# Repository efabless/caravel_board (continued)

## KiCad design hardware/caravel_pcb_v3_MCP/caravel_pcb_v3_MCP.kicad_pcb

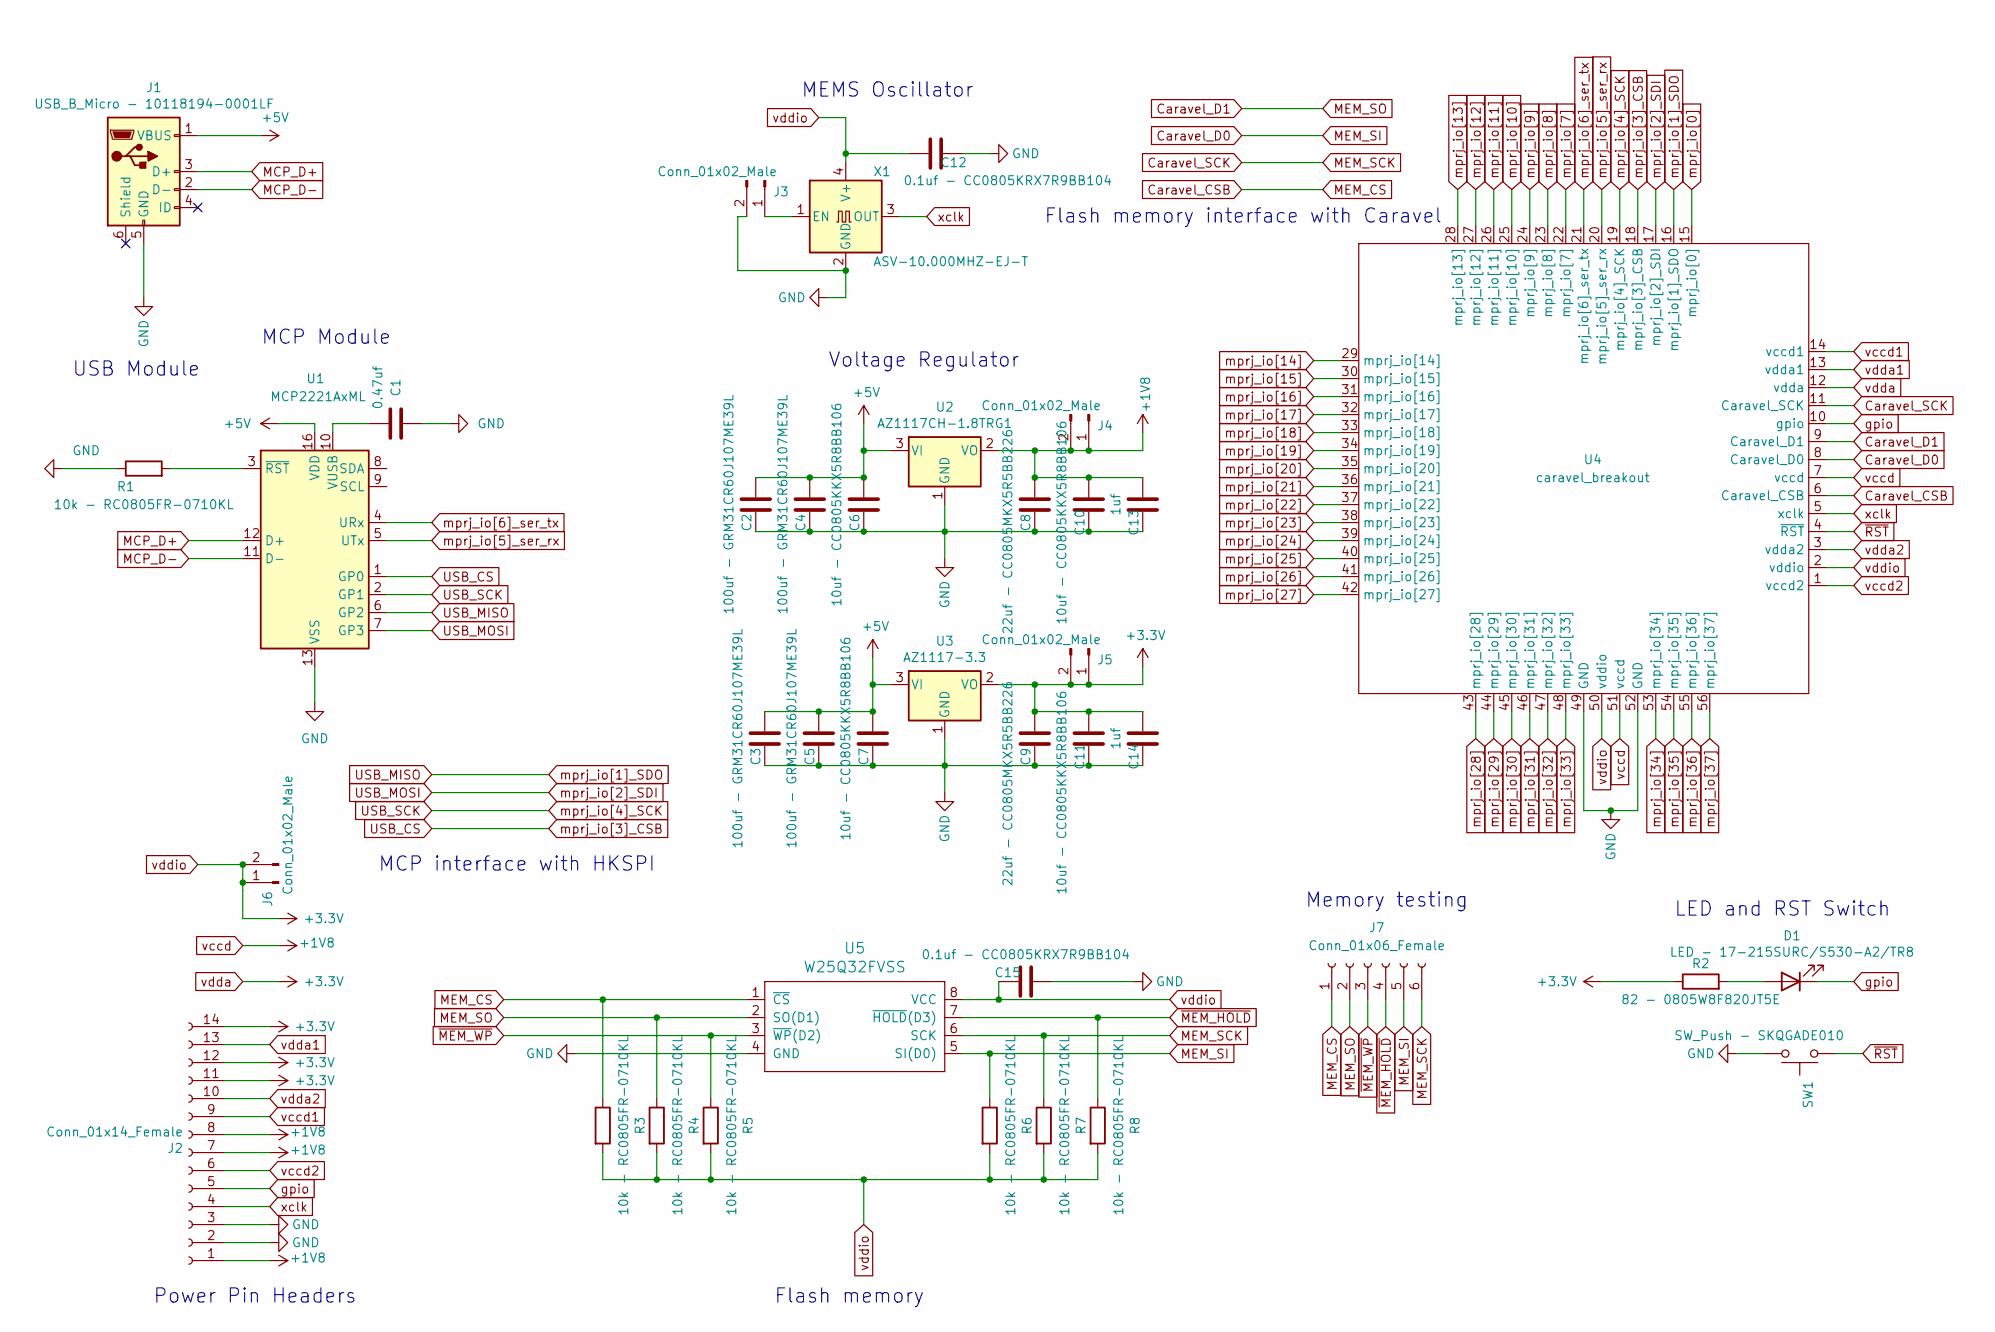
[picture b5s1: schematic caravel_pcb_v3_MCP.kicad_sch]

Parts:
C1: 0.47uf; C_0805_2012Metric
C2, C3, C4, C5: 100uf - GRM31CR60J107ME39L; C_1206_3216Metric
C6, C7, C10, C11: 10uf - CC0805KKX5R8BB106; C_0805_2012Metric
C8, C9: 22uf - CC0805MKX5R5BB226; C_0805_2012Metric
C12, C15: 0.1uf - CC0805KRX7R9BB104; C_0805_2012Metric
C13, C14: 1uf; C_0805_2012Metric
D1: LED - 17-215SURC/S530-A2/TR8; LED_1206_3216Metric
J1: USB_B_Micro - 10118194-0001LF; USB_Micro-B_Amphenol_10118194_Horizontal
J2: Conn_01x14_Female; PinHeader_1x14_P2.54mm_Vertical
J3, J4, J5, J6: Conn_01x02_Male; PinHeader_1x02_P2.54mm_Vertical
J7: Conn_01x06_Female; PinSocket_1x06_P2.54mm_Vertical
R1, R3, R4, R5, R6, R7, R8: 10k - RC0805FR-0710KL; R_0805_2012Metric
R2: 82 - 0805W8F820JT5E; R_0805_2012Metric
SW1: SW_Push - SKQGADE010; SW_SPST_SKQG_WithStem
U1: MCP2221AxML; QFN-16-1EP_4x4mm_P0.65mm_EP2.5x2.5mm
U2: AZ1117CH-1.8TRG1; SOT-223-3_TabPin2
U3: AZ1117-3.3; SOT-223-3_TabPin2
U4: caravel_breakout; caravel_breakout_v1
U5: W25Q32FVSS; SOIC-8_5.23x5.23mm_P1.27mm
X1: ASV-10.000MHZ-EJ-T; Oscillator_SMD_Abracon_ASV-4Pin_7.0x5.1mm

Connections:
+5V: C2.2, C3.2, C4.2, C5.2, C6.2, C7.2, J1.1 (VBUS), U1.16 (VDD), U2.3 (VI), U3.3 (VI)
Caravel_CSB: J7.1, R3.1, U4.6 (Caravel_CSB), U5.1 (~CS)
Caravel_D0: J7.5, R6.1, U4.8 (Caravel_D0), U5.5 (SI(D0))
Caravel_D1: J7.2, R4.1, U4.9 (Caravel_D1), U5.2 (SO(D1))
Caravel_SCK: J7.6, R7.1, U4.11 (Caravel_SCK), U5.6 (SCK)
GND: C1.2, C2.1, C3.1, C4.1, C5.1, C6.1, C7.1, C8.1, C9.1, C10.1, C11.1, C12.1, C13.1, C14.1, C15.2, J1.5 (GND), J2.2, J2.3, J3.2, R1.1, SW1.2, U1.13 (VSS), U2.1 (GND), U3.1 (GND), U4.49 (GND), U4.52 (GND), U5.4 (GND), X1.2 (GND)
MCP_D+: J1.3 (D+), U1.12 (D+)
MCP_D-: J1.2 (D-), U1.11 (D-)
unnamed: C1.1, U1.10 (VUSB)
unnamed: D1.2 (A), R2.2
unnamed: J3.1, X1.1 (EN)
unnamed: R1.2, U1.3 (~RST)
USB_CS: U1.1 (GP0), U4.18 (mprj_io[3]_CSB)
USB_MISO: U1.6 (GP2), U4.16 (mprj_io[1]_SDO)
USB_MOSI: U1.7 (GP3), U4.17 (mprj_io[2]_SDI)
USB_SCK: U1.2 (GP1), U4.19 (mprj_io[4]_SCK)
gpio: D1.1 (K), J2.5, U4.10 (gpio)
mprj_io[0]: U4.15 (mprj_io[0])
mprj_io[5]_ser_rx: U1.5 (UTx), U4.20 (mprj_io[5]_ser_rx)
mprj_io[6]_ser_tx: U1.4 (URx), U4.21 (mprj_io[6]_ser_tx)
mprj_io[7]: U4.22 (mprj_io[7])
mprj_io[8]: U4.23 (mprj_io[8])
mprj_io[9]: U4.24 (mprj_io[9])
mprj_io[10]: U4.25 (mprj_io[10])
mprj_io[11]: U4.26 (mprj_io[11])
mprj_io[12]: U4.27 (mprj_io[12])
mprj_io[13]: U4.28 (mprj_io[13])
mprj_io[14]: U4.29 (mprj_io[14])
mprj_io[15]: U4.30 (mprj_io[15])
mprj_io[16]: U4.31 (mprj_io[16])
mprj_io[17]: U4.32 (mprj_io[17])
mprj_io[18]: U4.33 (mprj_io[18])
mprj_io[19]: U4.34 (mprj_io[19])
mprj_io[20]: U4.35 (mprj_io[20])
mprj_io[21]: U4.36 (mprj_io[21])
mprj_io[22]: U4.37 (mprj_io[22])
mprj_io[23]: U4.38 (mprj_io[23])
mprj_io[24]: U4.39 (mprj_io[24])
mprj_io[25]: U4.40 (mprj_io[25])
mprj_io[26]: U4.41 (mprj_io[26])
mprj_io[27]: U4.42 (mprj_io[27])
mprj_io[28]: U4.43 (mprj_io[28])
mprj_io[29]: U4.44 (mprj_io[29])
mprj_io[30]: U4.45 (mprj_io[30])
mprj_io[31]: U4.46 (mprj_io[31])
mprj_io[32]: U4.47 (mprj_io[32])
mprj_io[33]: U4.48 (mprj_io[33])
mprj_io[34]: U4.53 (mprj_io[34])
mprj_io[35]: U4.54 (mprj_io[35])
mprj_io[36]: U4.55 (mprj_io[36])
mprj_io[37]: U4.56 (mprj_io[37])
vccd: C8.2, C10.2, C13.2, J2.1, J2.7, J2.8, J4.1, J4.2, U2.2 (VO), U4.7 (vccd), U4.51 (vccd)
vccd1: J2.9, U4.14 (vccd1)
vccd2: J2.6, U4.1 (vccd2)
vdda: C9.2, C11.2, C12.2, C14.2, C15.1, J2.11, J2.12, J2.14, J5.1, J5.2, J6.1, J6.2, R2.1, R3.2, R4.2, R5.2, R6.2, R7.2, R8.2, U3.2 (VO), U4.2 (vddio), U4.12 (vdda), U4.50 (vddio), U5.8 (VCC), X1.4 (V+)
vdda1: J2.13, U4.13 (vdda1)
vdda2: J2.10, U4.3 (vdda2)
xclk: J2.4, U4.5 (xclk), X1.3 (OUT)
~MEM_HOLD: J7.4, R8.1, U5.7 (~HOLD(D3))
~MEM_WP: J7.3, R5.1, U5.3 (~WP(D2))
~RST: SW1.1, U4.4 (~RST)

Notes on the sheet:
Voltage Regulator
MCP interface with HKSPI
Flash memory
Flash memory interface with Caravel
LED and RST Switch
Power Pin Headers
USB Module
MEMS Oscillator
Memory testing
MCP Module

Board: 2 copper layers, 38 parts (0 on the bottom side), 29 nets, no tracks yet.

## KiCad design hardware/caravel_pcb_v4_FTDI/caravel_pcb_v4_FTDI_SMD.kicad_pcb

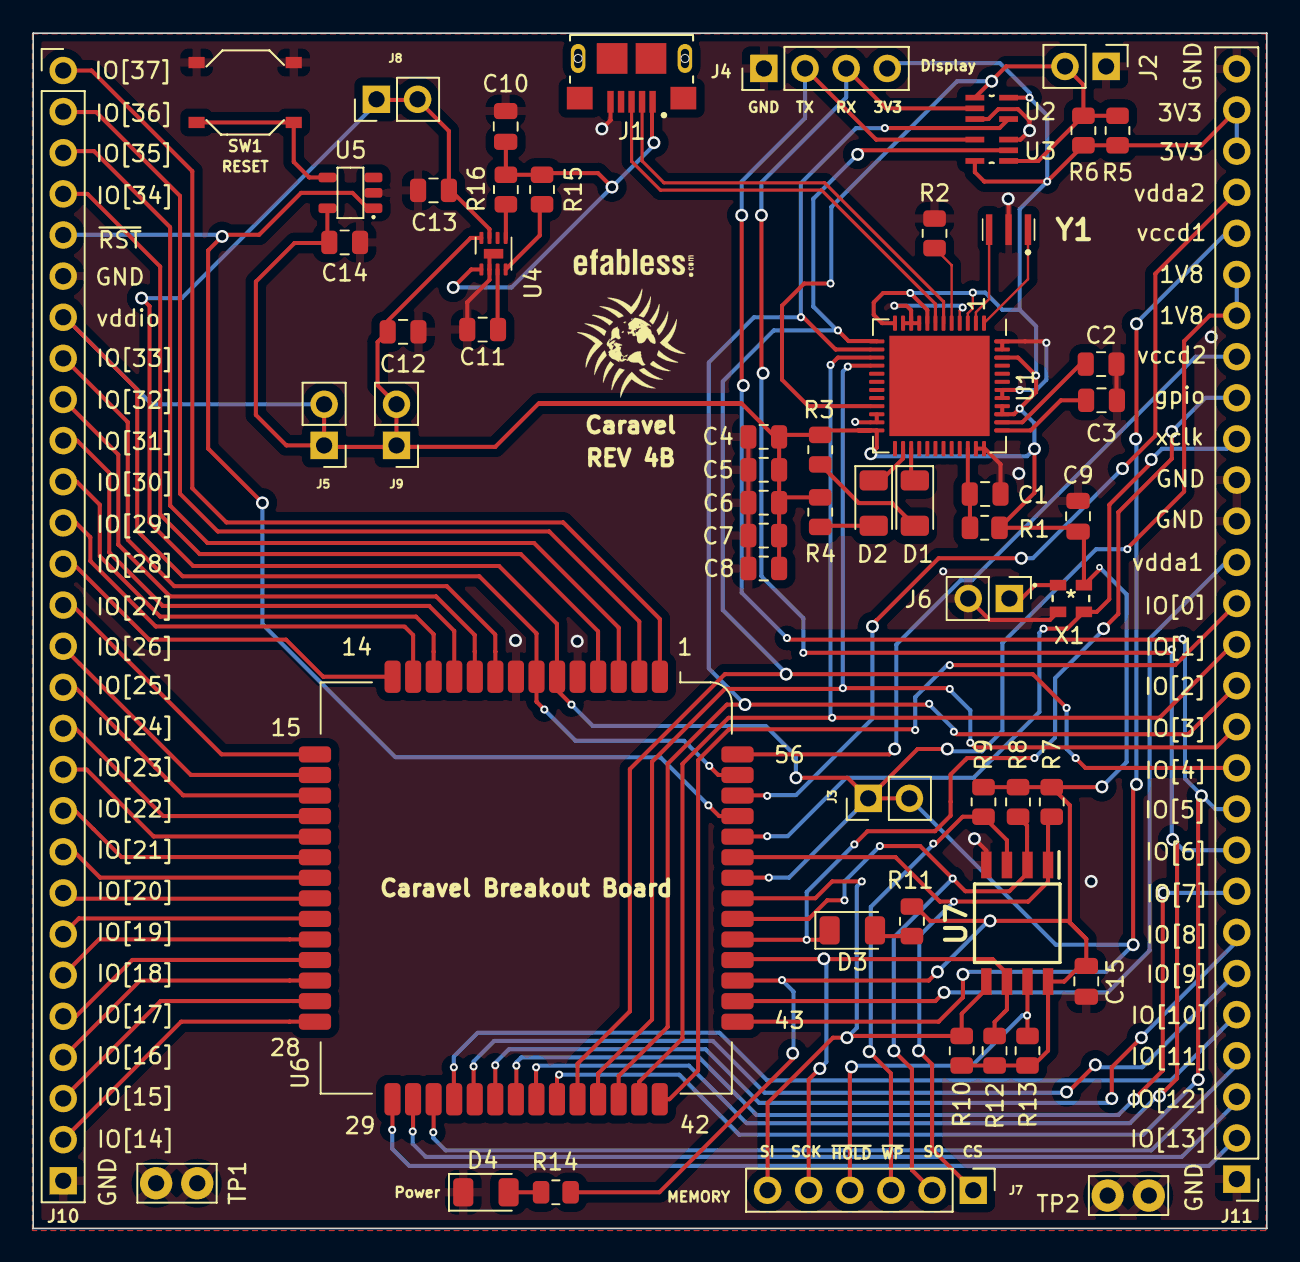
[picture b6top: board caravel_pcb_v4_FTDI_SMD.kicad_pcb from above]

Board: 2 copper layers, 76.2 x 73.8 mm, 60 parts (0 on the bottom side), 74 nets.

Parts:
C1: 0.01uf - CC0805JRX7R9BB103; C_0805_2012Metric
C2, C3, C4, C5, C6, C7, C8, C9, C11, C14, C15: 0.1uf - CC0805KRX7R9BB104; C_0805_2012Metric
C10: 10uf - CC0805KKX5R8BB106; C_0805_2012Metric
C12, C13: 2.2uf - CC0805MKX5R6BB225; C_0805_2012Metric
D1, D2, D3, D4: LED - 17-215SURC/S530-A2/TR8; LED_1206_3216Metric
J1: USB_B_Micro - 10118193-0001LF; FCI_10118193-0001LF
J2: Conn_01x02_Female; PinHeader_1x02_P2.54mm_Vertical
J3, J5, J6, J8, J9: Conn_01x02_Male; PinHeader_1x02_P2.54mm_Vertical
J4: Conn_01x04_Female; PinHeader_1x04_P2.54mm_Vertical
J7: Conn_01x06_Female; PinHeader_1x06_P2.54mm_Vertical
J10: Conn_01x27_Female; PinHeader_1x28_P2.54mm_Vertical
J11: Conn_01x20_Female; PinHeader_1x28_P2.54mm_Vertical
R1, R7, R8, R9, R10, R12, R13: 10k - RC0805FR-0710KL; R_0805_2012Metric
R2: 12K 1% - 0805W8F1202T5E; R_0805_2012Metric
R3, R4: 150 - 0805W8J0151T5E; R_0805_2012Metric
R5, R6, R15, R16: 10k; R_0805_2012Metric
R11, R14: 82 - 0805W8F820JT5E; R_0805_2012Metric
SW1: SW_Push - SKQGADE010; SW4-SMD-5.2X5.2X1.5MM
T1: Logo; logo
T2: Logo; ef_logo
TP1, TP2: TestPoint; TestPoint_Bridge_Pitch2.54mm_Drill1.0mm
U1: FT232H; QFN-48-1EP_8x8mm_P0.5mm_EP6.2x6.2mm
U2, U3: SN74LVC1G125DCKR; SOT65P210X110-5N
U4: MIC5350-SGYMT-TR; DFN-8-1EP_2x2mm_P0.5mm_EP0.6x1.2mm
U5: MCP1319MT-29LE-OT; PoR_5_SOT23
U6: caravel_breakout; caravel_breakout_SMD
U7: W25Q32FVSS; SOIC127P790X216-8N
X1: DSC6001_10MHZ; DSC6001JE1A-010.0000
Y1: CSTNE12M0GH5L000R0

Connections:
+5V: C10.2, J1.1 (VBUS), R15.2, R16.2, U4.1 (VIN)
Caravel_CSB: J7.1, R7.1, U6.51 (Caravel_CSB), U7.1 (~CS)
Caravel_D0: J7.6, R10.1, U6.49 (Caravel_D0), U7.5 (SI(D0))
Caravel_D1: J7.2, R8.1, U6.48 (Caravel_D1), U7.2 (SO(D1))
Caravel_SCK: J7.5, R12.1, U6.46 (Caravel_SCK), U7.6 (SCK)
FTDI_D+: J1.3 (D+), U1.7 (DP)
FTDI_D-: J1.2 (D-), U1.6 (DM)
GND: C1.1, C2.1, C3.1, C4.1, C5.1, C6.1, C7.1, C8.1, C9.1, C10.1, C11.2, C12.1, C13.1, C14.1, C15.2, D4.1 (K), J1.5 (GND), J2.1, J4.1, J6.2, J10.6, J10.28, J11.1, J11.17, J11.18, J11.28, R2.1, SW1.2, TP1.1, TP2.1, U1.4 (AGND), U1.9 (AGND), U1.10 (GND), U1.11 (GND), U1.22 (GND), U1.23 (GND), U1.35 (GND), U1.36 (GND), U1.41 (AGND), U1.42 (TEST), U1.47 (GND), U1.48 (GND), U2.3 (GND), U3.3 (GND), U4.2 (GND), U4.9 (GND), U5.2 (VSS), U6.5 (GND), U6.8 (GND), U7.4 (GND), X1.2 (GND), Y1.2
unnamed: C1.2, R1.1, U1.34 (~RESET)
unnamed: C2.2, U1.38 (VCCCORE)
unnamed: C3.2, U1.37 (VCCA)
unnamed: C11.1, U4.3 (BYP)
unnamed: D1.1 (K), U1.27 (ACBUS3)
unnamed: D1.2 (A), R3.1
unnamed: D2.1 (K), U1.26 (ACBUS2)
unnamed: D2.2 (A), R4.1
unnamed: D3.2 (A), R11.2
unnamed: D4.2 (A), R14.2
unnamed: J6.1, X1.1 (EN)
unnamed: R2.2, U1.5 (REF)
unnamed: R15.1, U4.4 (EN2)
unnamed: R16.1, U4.5 (EN1)
unnamed: U1.1 (XCSI), Y1.1
unnamed: U1.2 (XCSO), Y1.3
UART_EN: J2.2, R5.2, R6.2, U1.21 (ACBUS0), U2.1 (~OE), U3.1 (~OE)
USB_CS1: J11.12, U1.16 (ADBUS3), U6.39 (mprj_io[3]_CSB)
USB_SCK_TXD: J11.11, U1.13 (ADBUS0), U3.2 (A), U6.38 (mprj_io[4]_SCK)
USB_SI: J11.14, U1.15 (ADBUS2), U6.41 (mprj_io[1]_SDO)
USB_SO_RXD: J11.13, U1.14 (ADBUS1), U2.4 (Y), U6.40 (mprj_io[2]_SDI)
gpio: D3.1 (K), J11.20, U6.47 (gpio)
mprj_io[0]: J11.15, U6.42 (mprj_io[0])
mprj_io[5]_ser_rx: J4.2, J11.10, U3.4 (Y), U6.37 (mprj_io[5]_ser_rx)
mprj_io[6]_ser_tx: J4.3, J11.9, U2.2 (A), U6.36 (mprj_io[6]_ser_tx)
mprj_io[7]: J11.8, U6.35 (mprj_io[7])
mprj_io[8]: J11.7, U6.34 (mprj_io[8])
mprj_io[9]: J11.6, U6.33 (mprj_io[9])
mprj_io[10]: J11.5, U6.32 (mprj_io[10])
mprj_io[11]: J11.4, U6.31 (mprj_io[11])
mprj_io[12]: J11.3, U6.30 (mprj_io[12])
mprj_io[13]: J11.2, U6.29 (mprj_io[13])
mprj_io[14]: J10.27, U6.28 (mprj_io[14])
mprj_io[15]: J10.26, U6.27 (mprj_io[15])
mprj_io[16]: J10.25, U6.26 (mprj_io[16])
mprj_io[17]: J10.24, U6.25 (mprj_io[17])
mprj_io[18]: J10.23, U6.24 (mprj_io[18])
mprj_io[19]: J10.22, U6.23 (mprj_io[19])
mprj_io[20]: J10.21, U6.22 (mprj_io[20])
mprj_io[21]: J10.20, U6.21 (mprj_io[21])
mprj_io[22]: J10.19, U6.20 (mprj_io[22])
mprj_io[23]: J10.18, U6.19 (mprj_io[23])
mprj_io[24]: J10.17, U6.18 (mprj_io[24])
mprj_io[25]: J10.16, U6.17 (mprj_io[25])
mprj_io[26]: J10.15, U6.16 (mprj_io[26])
mprj_io[27]: J10.14, U6.15 (mprj_io[27])
mprj_io[28]: J10.13, U6.14 (mprj_io[28])
mprj_io[29]: J10.12, U6.13 (mprj_io[29])
mprj_io[30]: J10.11, U6.12 (mprj_io[30])
mprj_io[31]: J10.10, U6.11 (mprj_io[31])
mprj_io[32]: J10.9, U6.10 (mprj_io[32])
mprj_io[33]: J10.8, U6.9 (mprj_io[33])
mprj_io[34]: J10.4, U6.4 (mprj_io[34])
mprj_io[35]: J10.3, U6.3 (mprj_io[35])
mprj_io[36]: J10.2, U6.2 (mprj_io[36])
mprj_io[37]: J10.1, U6.1 (mprj_io[37])
vccd: C13.2, J3.1, J3.2, J8.1, J8.2, J11.22, J11.23, J11.24, U4.7 (VOUT2), U6.6 (vccd), U6.43 (vccd1), U6.50 (vccd)
vccd2: J11.21, U6.56 (vccd2)
vdda: C4.2, C5.2, C6.2, C7.2, C8.2, C9.2, C12.2, C14.2, C15.1, J4.4, J5.1, J5.2, J9.1, J9.2, J10.7, J11.26, J11.27, R1.2, R3.2, R4.2, R5.1, R6.1, R7.2, R8.2, R9.2, R10.2, R11.1, R12.2, R13.2, R14.1, U1.3 (VPHY), U1.8 (VPLL), U1.12 (VCCIO), U1.24 (VCCIO), U1.39 (VCCD), U1.40 (VREGIN), U1.46 (VCCIO), U2.5 (VCC), U3.5 (VCC), U4.8 (VOUT1), U5.5 (VDD), U6.7 (vddio), U6.45 (vdda), U6.55 (vddio), U7.8 (VCC), X1.4 (V+)
vdda1: J11.16, U6.44 (vdda1)
vdda2: J11.25, U6.54 (vdda2)
xclk: J11.19, U6.52 (xclk), X1.3 (OUT)
~MEM_HOLD: J7.4, R13.1, U7.7 (~HOLD(D3))
~MEM_WP: J7.3, R9.1, U7.3 (~WP(D2))
~MR: SW1.1, U5.4 (~MR)
~RST: J10.5, U5.1 (~RST), U6.53 (~RST)
